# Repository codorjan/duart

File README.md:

# DUART Dual Serial Board Designed For RC2014

This is an XR88C681-based serial interface card designed for the RC2014 microcomputer system. This provides two serial interfaces to an RC2014 system in addition to a 16-bit counter/timer and several general-purpose input and output lines.

The board has undergone limited testing with the [SCM](https://smallcomputercentral.wordpress.com/small-computer-monitor/small-computer-monitor-v1-0/) driver written by Colin MacArthur for Tadeusz Pycio's [XR88C681 board](https://groups.google.com/forum/#!topic/retro-comp/5gGqL3yGzyA) (and it should be fully software compatible with it).

A driver has been incorporated into the dev branch of [RomWBW](https://github.com/wwarthen/RomWBW). This is not currently built into the standard RC2014 ROM but is available in the RCZ80_duart configuration.

## Build Notes

Until this is properly documented, refer to the [schematic](duart.pdf).

The values and types of most components are not critical. Capacitors C1-C6 (100nF, MLCC) are power bypass/decoupling capacitors for each IC and C7 (10µF, electrolytic) provides additional transient decoupling for the DUART itself. RN1 and RN4 (100kΩ) are bussed resistor networks intended to act as pull-ups for the chip select logic (RN1) and to prevent the general purpose inputs (and IM2-specific interrupt lines) from floating (RN4). RN2 and RN3 (1kΩ) are isolated resistor networks intended to provide short-circuit protection to the serial I/O lines. R1 and R2 (100kΩ) pull the serial receive input lines up to their idle state. R3 and R4 (100kΩ) pull the serial /CTS input lines down to their active state.

Oscillator X1 and capacitor C5 are optional in a standard RC2014 system with a 7.3728MHz clock. In this case JP5 should be closed and pins 3 and 4 (CLKDIV2) of JP1 should be bridged with jumpers to provided the DUART with its expected 3.6864MHz clock.

## License

Copyright 2019-2020 Chris Odorjan

This work is licensed under a [Creative Commons Attribution-ShareAlike 4.0 International License](http://creativecommons.org/licenses/by-sa/4.0/).

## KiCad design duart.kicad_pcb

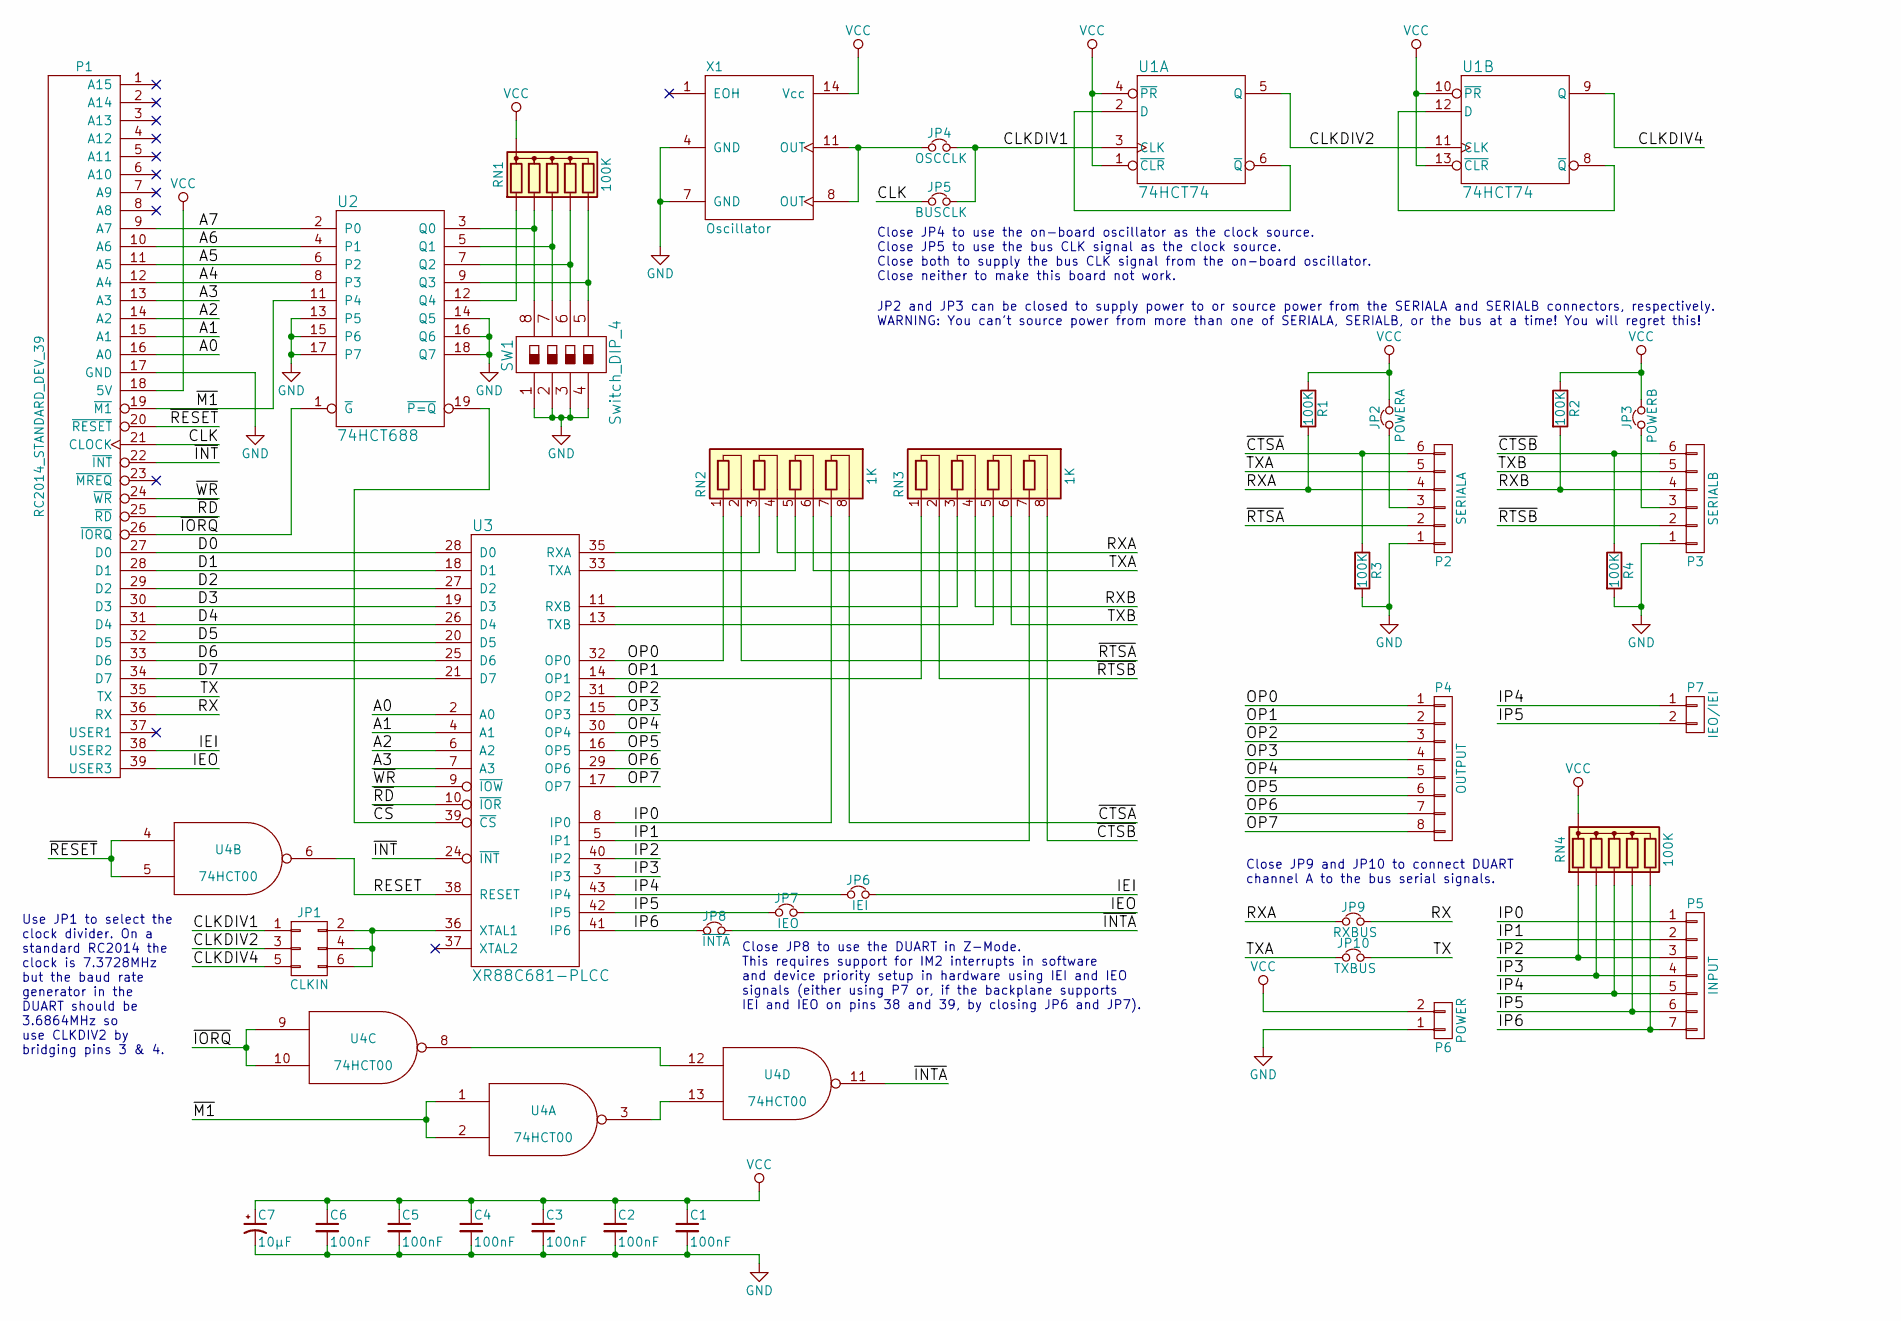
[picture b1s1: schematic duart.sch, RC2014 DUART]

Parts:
C1, C2, C3, C4, C5, C6: 100nF; C_Rect_L4.6mm_W2.0mm_P2.50mm_MKS02_FKP02
C7: 10µF; CP_Radial_D5.0mm_P2.00mm
JP1: CLKIN; PinHeader_2x03_P2.54mm_Vertical
JP2: POWERA; PinHeader_1x02_P2.54mm_Vertical
JP3: POWERB; PinHeader_1x02_P2.54mm_Vertical
JP4: OSCCLK; PinHeader_1x02_P2.54mm_Vertical
JP5: BUSCLK; PinHeader_1x02_P2.54mm_Vertical
JP6: IEI; PinHeader_1x02_P2.54mm_Vertical
JP7: IEO; PinHeader_1x02_P2.54mm_Vertical
JP8: ~INTA; PinHeader_1x02_P2.54mm_Vertical
JP9: RXBUS; PinHeader_1x02_P2.54mm_Vertical
JP10: TXBUS; PinHeader_1x02_P2.54mm_Vertical
P1: RC2014_STANDARD_DEV_39; PinHeader_1x39_P2.54mm_Vertical
P2: SERIALA; PinHeader_1x06_P2.54mm_Vertical
P3: SERIALB; PinHeader_1x06_P2.54mm_Vertical
P4: OUTPUT; PinHeader_1x08_P2.54mm_Vertical
P5: INPUT; PinHeader_1x07_P2.54mm_Vertical
P6: POWER; PinHeader_1x02_P2.54mm_Vertical
P7: IEO/IEI; PinHeader_1x02_P2.54mm_Vertical
R1, R2, R3, R4: 100K; R_Axial_DIN0207_L6.3mm_D2.5mm_P7.62mm_Horizontal
RN1, RN4: 100K; R_Array_SIP6
RN2, RN3: 1K; R_Array_SIP8
SW1: Switch_DIP_4; SW_DIP_SPSTx04_Piano_10.8x11.72mm_W7.62mm_P2.54mm
U1: 74HCT74; DIP-14_W7.62mm_Socket
U2: 74HCT688; DIP-20_W7.62mm_Socket
U3: XR88C681-PLCC; PLCC-44_THT-Socket
U4: 74HCT00; DIP-14_W7.62mm_Socket
X1: Oscillator; DIP-14_W7.62mm_Socket

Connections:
/A0: P1.16 (A0), U3.2 (A0)
/A1: P1.15 (A1), U3.4 (A1)
/A2: P1.14 (A2), U3.6 (A2)
/A3: P1.13 (A3), U3.7 (A3)
/A4: P1.12 (A4), U2.8 (P3)
/A5: P1.11 (A5), U2.6 (P2)
/A6: P1.10 (A6), U2.4 (P1)
/A7: P1.9 (A7), U2.2 (P0)
/CLK: JP5.1, P1.21 (CLOCK)
/CLKDIV1: JP1.1, JP4.2, JP5.2, U1.3 (CLK)
/CLKDIV2: JP1.3, U1.5 (Q), U1.11 (CLK)
/CLKDIV4: JP1.5, U1.9 (Q)
/D0: P1.27 (D0), U3.28 (D0)
/D1: P1.28 (D1), U3.18 (D1)
/D2: P1.29 (D2), U3.27 (D2)
/D3: P1.30 (D3), U3.19 (D3)
/D4: P1.31 (D4), U3.26 (D4)
/D5: P1.32 (D5), U3.20 (D5)
/D6: P1.33 (D6), U3.25 (D6)
/D7: P1.34 (D7), U3.21 (D7)
/IEI: JP6.2, P1.38 (USER2)
/IEO: JP7.2, P1.39 (USER3)
/IP0: P5.1, RN2.7 (R4.1), U3.8 (IP0)
/IP1: P5.2, RN3.7 (R4.1), U3.5 (IP1)
/IP2: P5.3, RN4.2 (R1), U3.40 (IP2)
/IP3: P5.4, RN4.3 (R2), U3.3 (IP3)
/IP4: JP6.1, P5.5, P7.1, RN4.4 (R3), U3.43 (IP4)
/IP5: JP7.1, P5.6, P7.2, RN4.5 (R4), U3.42 (IP5)
/IP6: JP8.1, P5.7, RN4.6 (R5), U3.41 (IP6)
/OP0: P4.1, RN2.1 (R1.1), U3.32 (OP0)
/OP1: P4.2, RN3.1 (R1.1), U3.14 (OP1)
/OP2: P4.3, U3.31 (OP2)
/OP3: P4.4, U3.15 (OP3)
/OP4: P4.5, U3.30 (OP4)
/OP5: P4.6, U3.16 (OP5)
/OP6: P4.7, U3.29 (OP6)
/OP7: P4.8, U3.17 (OP7)
/RESET: U3.38 (RESET), U4.6
/RX: JP9.2, P1.36 (RX)
/RXA: JP9.1, P2.4, R1.2, RN2.4 (R2.2)
/RXB: P3.4, R2.2, RN3.4 (R2.2)
/TX: JP10.2, P1.35 (TX)
/TXA: JP10.1, P2.5, RN2.6 (R3.2)
/TXB: P3.5, RN3.6 (R3.2)
/~CS: U2.19 (~P=Q), U3.39 (~CS)
/~CTSA: P2.6, R3.1, RN2.8 (R4.2)
/~CTSB: P3.6, R4.1, RN3.8 (R4.2)
/~INT: P1.22 (~INT), U3.24 (~INT)
/~INTA: JP8.2, U4.11
/~IORQ: P1.26 (~IORQ), U2.1 (~G), U4.9, U4.10
/~M1: P1.19 (~M1), U2.11 (P4), U4.1, U4.2
/~RD: P1.25 (~RD), U3.10 (~IOR)
/~RESET: P1.20 (~RESET), U4.4, U4.5
/~RTSA: P2.2, RN2.2 (R1.2)
/~RTSB: P3.2, RN3.2 (R1.2)
/~WR: P1.24 (~WR), U3.9 (~IOW)
GND: C1.2, C2.2, C3.2, C4.2, C5.2, C6.2, C7.2, P1.17 (GND), P2.1, P3.1, P6.1, R3.2, R4.2, SW1.1, SW1.2, SW1.3, SW1.4, U1.7 (GND), U2.10 (GND), U2.13 (P5), U2.14 (Q5), U2.15 (P6), U2.16 (Q6), U2.17 (P7), U2.18 (Q7), U3.22 (GND), U4.7 (GND), X1.4 (GND), X1.7 (GND)
unnamed: JP1.2, JP1.4, JP1.6, U3.36 (XTAL1)
unnamed: JP2.1, P2.3
unnamed: JP3.1, P3.3
unnamed: JP4.1, X1.8 (OUT), X1.11 (OUT)
unnamed: RN1.2 (R1), U2.12 (Q4)
unnamed: RN1.3 (R2), SW1.8, U2.3 (Q0)
unnamed: RN1.4 (R3), SW1.7, U2.5 (Q1)
unnamed: RN1.5 (R4), SW1.6, U2.7 (Q2)
unnamed: RN1.6 (R5), SW1.5, U2.9 (Q3)
unnamed: RN2.3 (R2.1), U3.35 (RXA)
unnamed: RN2.5 (R3.1), U3.33 (TXA)
unnamed: RN3.3 (R2.1), U3.11 (RXB)
unnamed: RN3.5 (R3.1), U3.13 (TXB)
unnamed: U1.2 (D), U1.6 (~Q)
unnamed: U1.8 (~Q), U1.12 (D)
unnamed: U4.8, U4.12
unnamed: U4.3, U4.13
VCC: C1.1, C2.1, C3.1, C4.1, C5.1, C6.1, C7.1, JP2.2, JP3.2, P1.18 (5V), P6.2, R1.1, R2.1, RN1.1 (common), RN4.1 (common), U1.1 (~CLR), U1.4 (~PR), U1.10 (~PR), U1.13 (~CLR), U1.14 (VCC), U2.20 (VCC), U3.44 (VCC), U4.14 (VCC), X1.14 (Vcc)

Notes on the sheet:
Close JP4 to use the on-board oscillator as the clock source. Close JP5 to use the bus CLK signal as the clock source. Close both to supply the bus CLK signal from the on-board oscillator. Close neither to make this board not work.
JP2 and JP3 can be closed to supply power to or source power from the SERIALA and SERIALB connectors, respectively. WARNING: You can't source power from more than one of SERIALA, SERIALB, or the bus at a time! You will regret this!
Close JP8 to use the DUART in Z-Mode. This requires support for IM2 interrupts in software and device priority setup in hardware using IEI and IEO signals (either using P7 or, if the backplane supports IEI and IEO on pins 38 and 39, by closing JP6 and JP7).
Close JP9 and JP10 to connect DUART channel A to the bus serial signals.
Use JP1 to select the clock divider. On a standard RC2014 the clock is 7.3728MHz but the baud rate generator in the DUART should be 3.6864MHz so use CLKDIV2 by bridging pins 3 & 4.

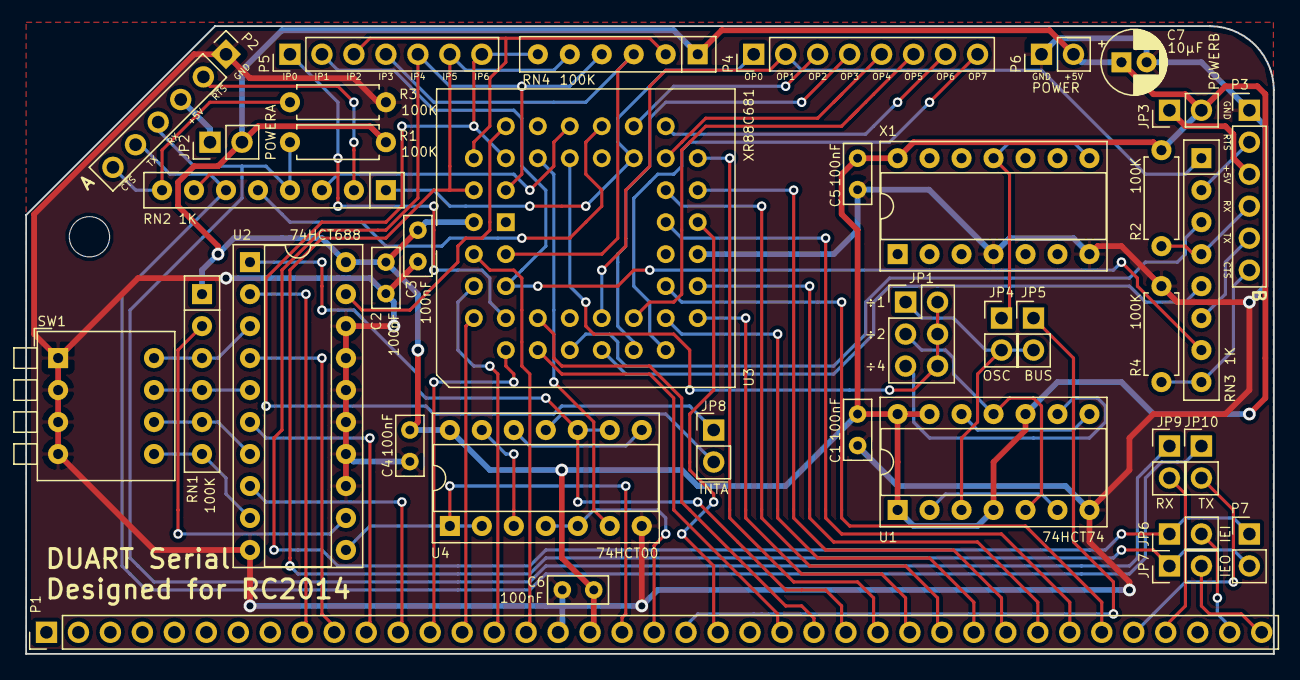
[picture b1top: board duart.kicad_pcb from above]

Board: 2 copper layers, 99.1 x 49.9 mm, 38 parts (0 on the bottom side), 75 nets.

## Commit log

2020-03-27 Create README.md
    rudimentary documentation
2020-03-28 add image of back of card (and rename front)
2020-03-28 add .gitignore and remove unnecessary backups
2020-03-28 add CC-BY-SA-4.0 license
2020-04-07 move JP4/JP5 and JP9/JP10 pairs closer together so 2x2 pin headers can be used
    adjust some text
    make references for C2 and C3 easier to read
    don't use tab characters in text, OSH Park renders it as a question mark
    add link to repository
2020-04-07 render gerbers
2020-04-09 add photos of board
2020-05-13 add datasheets
2020-06-01 don't use overkill quality settings on JPEG images
2020-06-07 mention RomWBW driver

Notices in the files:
duart.kicad_pcb:
©2019-2020 Chris Odorjan
